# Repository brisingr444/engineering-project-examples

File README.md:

# engineering-project-examples
Editable sample projects for SynthCrew, Workcell Foundry, SiliconForge, PowerSystem and TraceForge.

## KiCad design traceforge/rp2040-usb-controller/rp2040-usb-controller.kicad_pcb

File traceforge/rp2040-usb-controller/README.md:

[Download this editable project ZIP](rp2040-usb-controller.zip)

Extract the complete project folder before opening it. The source files are also available below.

ZIP SHA-256: `ee8aa9aada79eca28375414765a2e70979933c8f12b47b56a6a397c69c7f46b1`

# RP2040 USB-C Bench DAQ / Controller

An editable, USB-powered RP2040 bench design with four analogue inputs, eight digital I/O, I2C and SWD. The design starts with the leads: each analogue input on J2 has its ground beside it. The USB-C receptacle sits on a short edge; digital and analogue headers are on opposite sides of the board.

## Open and inspect

Extract the entire directory together. Open **rp2040-usb-controller.kicad_pro** in TraceForge or KiCad 10.0.5 with the standard KiCad 10 symbols and footprints installed. Open the schematic to follow a channel, then open the PCB to inspect the copper. In the PCB editor choose **View → 3D Viewer** (Alt+3). The supplied render uses the exact STEP resources named in the board; it is not a photograph.

With the matching stock 3D libraries installed, the standard paths work. To use just this package’s fourteen models on Linux without changing your global path, start a single KiCad session from this directory:

```sh
KICAD10_3DMODEL_DIR="$PWD/models" kicad rp2040-usb-controller.kicad_pro
```

On Windows, open a fresh PowerShell in the extracted directory, set `$env:KICAD10_3DMODEL_DIR = (Resolve-Path .\models).Path`, and start your installed KiCad executable from that shell with the .kicad_pro file. Closing that shell leaves the normal system setting unchanged.

## At the bench

**This is an unbuilt design reference**, not a tested device. See [the design notes and numbered header guide](PROJECT.md) for signal limits and intended use; [Bench-BOM.csv](Bench-BOM.csv) is editable. There is no firmware. Do not backfeed the 3V3 output or assume protection for inputs outside the specified range. Perform your own fabrication, electrical, fit and bring-up reviews.

## What the checks cover

The supplied PCB and schematic were read with KiCad 10.0.5. Enabled ERC, DRC and schematic-to-board parity reported no findings; the DRC report recorded no unconnected items. All 42 footprint origins, including four mounting holes, were inside the rectangular board outline. The 38 fitted references use the fourteen unique STEP models supplied here. This post-run visual check supplements the original engineering notes: the creator sandbox did not itself contain the model library.

The native full candidate suite reported **14 passed, 0 failed, 9 skipped**. [The suite summary](checks/agent-checks.json) names each check. The KiCad reports preserve their ignored-check lists: [ERC](checks/erc.json) and [DRC and parity](checks/drc-parity.json). No hardware performance, impedance measurement, enclosure mating tolerance or USB certification is claimed.

[Licence and attribution](ATTRIBUTION.md) · [TraceForge app download](https://traceforge.space/download/)

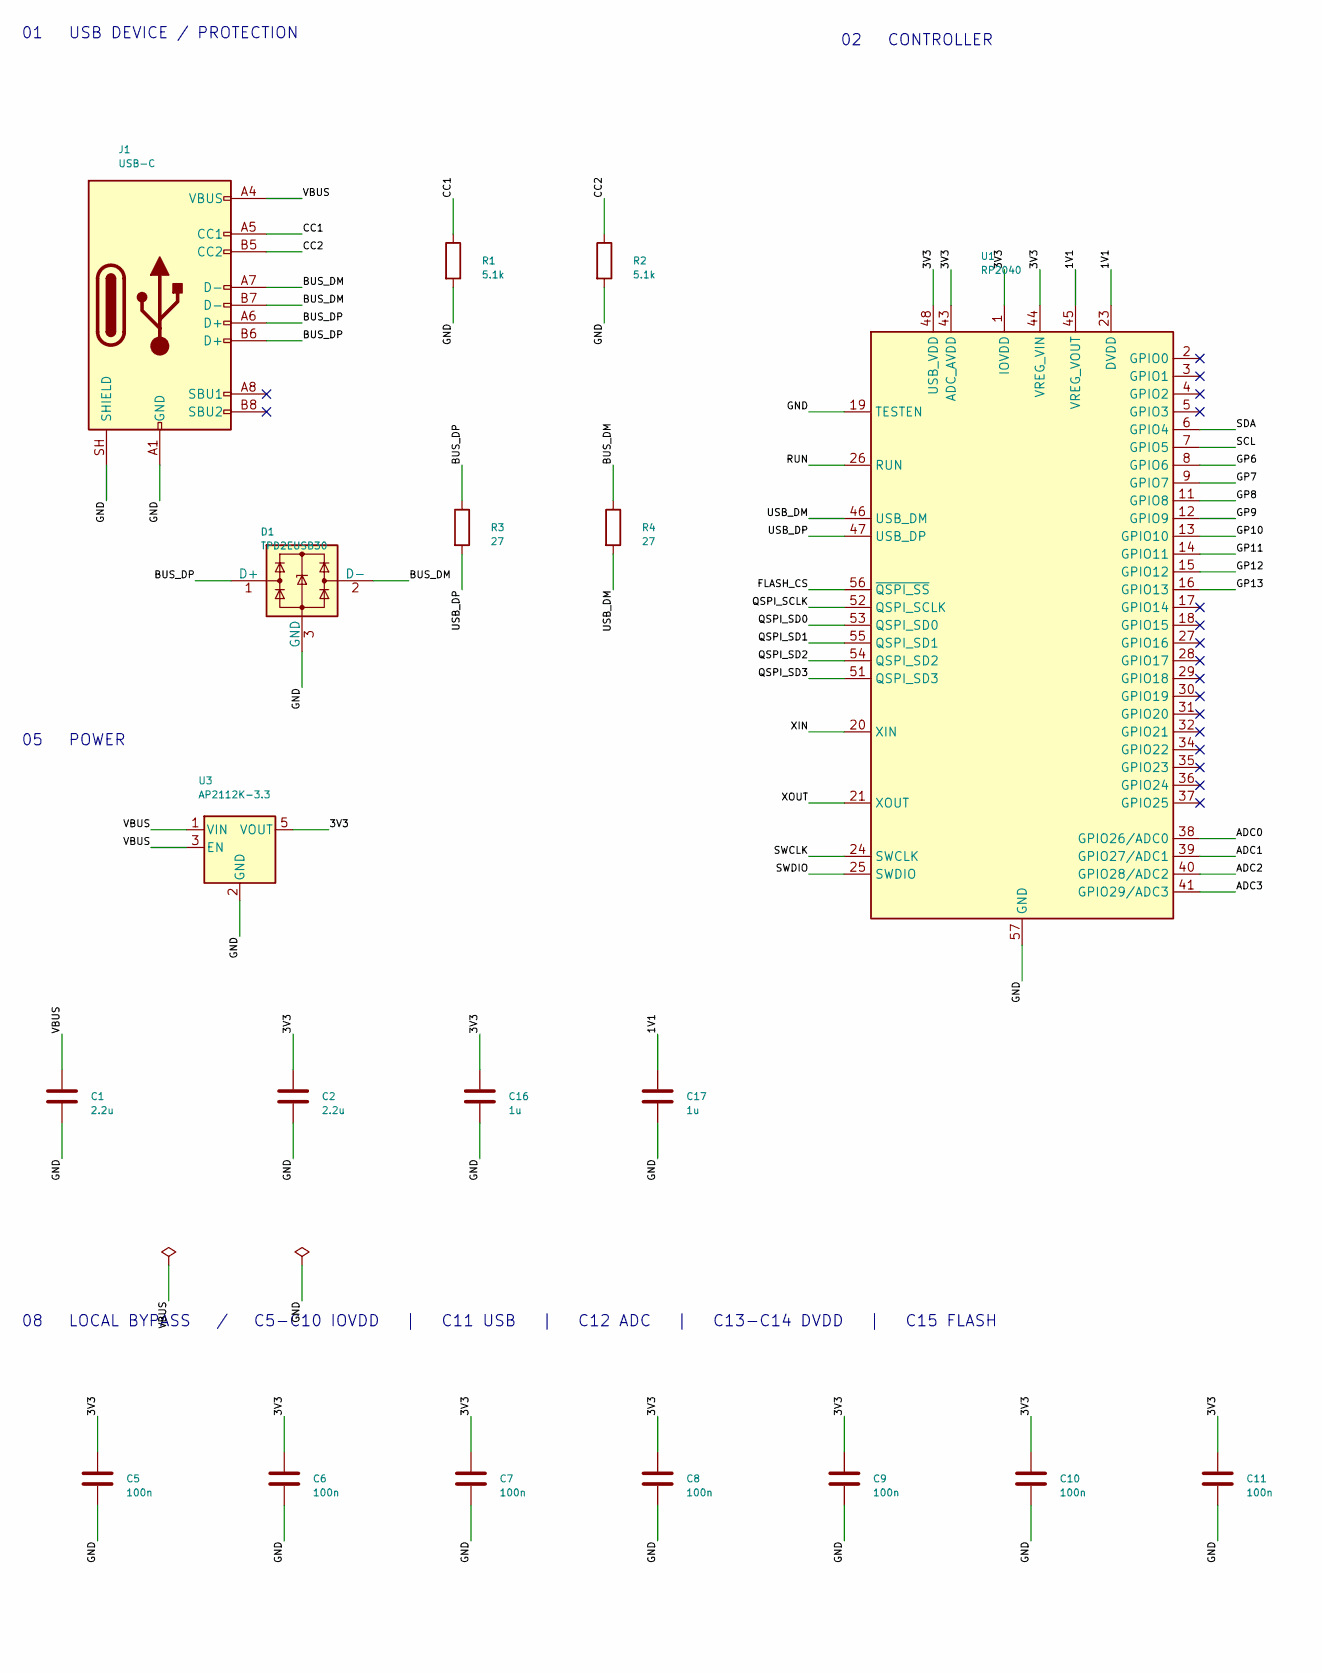
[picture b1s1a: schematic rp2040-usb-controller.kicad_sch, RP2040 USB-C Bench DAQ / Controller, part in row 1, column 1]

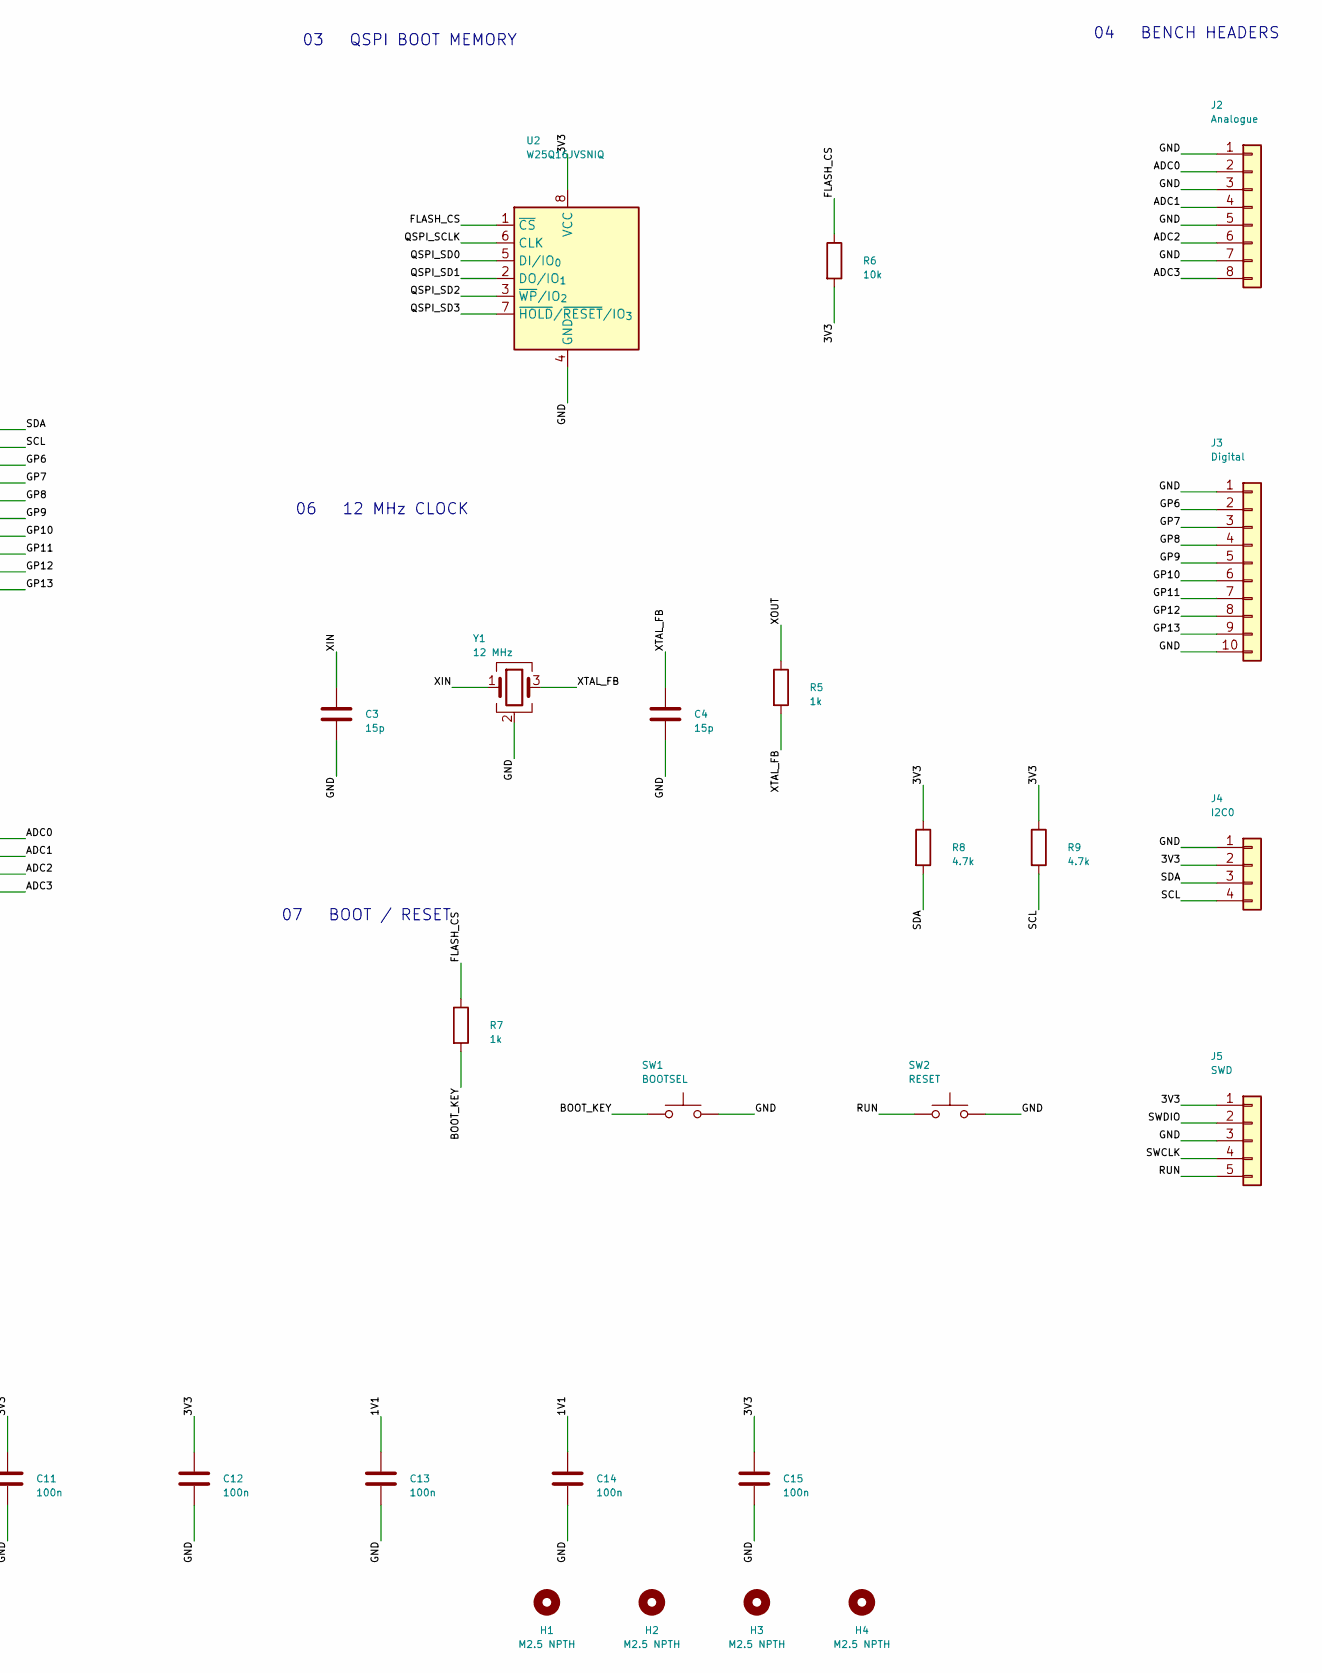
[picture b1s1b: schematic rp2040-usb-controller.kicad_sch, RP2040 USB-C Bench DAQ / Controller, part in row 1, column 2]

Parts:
C1, C2: 2.2u; C_0805_2012Metric; MPN GRM21BR71E225KA73L
C3, C4: 15p; C_0603_1608Metric; MPN GRM1885C1H150JA01D
C5, C6, C7, C8, C9, C10, C11, C12, C13, C14, C15: 100n; C_0603_1608Metric; MPN GRM188R71C104KA01D
C16, C17: 1u; C_0603_1608Metric; MPN GRM188R71C105KA12D
D1: TPD2EUSB30; Texas_DRT-3; MPN TPD2EUSB30DRTR
H1, H2, H3, H4: M2.5 NPTH; MountingHole_2.7mm_M2.5
J1: USB-C; USB_C_Receptacle_GCT_USB4085; MPN USB4085-GF-A
J2: Analogue; PinHeader_1x08_P2.54mm_Vertical; MPN TSW-008-07-G-S
J3: Digital; PinHeader_1x10_P2.54mm_Vertical; MPN TSW-010-07-G-S
J4: I2C0; PinHeader_1x04_P2.54mm_Vertical; MPN TSW-004-07-G-S
J5: SWD; PinHeader_1x05_P2.54mm_Vertical; MPN TSW-005-07-G-S
R1, R2: 5.1k; R_0603_1608Metric; MPN RC0603FR-075K1L
R3, R4: 27; R_0603_1608Metric; MPN RC0603FR-0727RL
R5, R7: 1k; R_0603_1608Metric; MPN RC0603FR-071KL
R6: 10k; R_0603_1608Metric; MPN RC0603FR-0710KL
R8, R9: 4.7k; R_0603_1608Metric; MPN RC0603FR-074K7L
SW1: BOOTSEL; SW_Push_1P1T_NO_CK_KMR2; MPN KMR221GLFS
SW2: RESET; SW_Push_1P1T_NO_CK_KMR2; MPN KMR221GLFS
U1: RP2040; QFN-56-1EP_7x7mm_P0.4mm_EP3.2x3.2mm; MPN RP2040
U2: W25Q16JVSNIQ; SOIC-8_3.9x4.9mm_P1.27mm; MPN W25Q16JVSNIQ
U3: AP2112K-3.3; SOT-23-5; MPN AP2112K-3.3TRG1
Y1: 12 MHz; Crystal_SMD_3225-4Pin_3.2x2.5mm; MPN ABM8-272-T3

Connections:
/1V1: C13.1, C14.1, C17.1, U1.23 (DVDD), U1.45 (VREG_VOUT), U1.50 (DVDD)
/3V3: C2.1, C5.1, C6.1, C7.1, C8.1, C9.1, C10.1, C11.1, C12.1, C15.1, C16.1, J4.2, J5.1, R6.2, R8.1, R9.1, U1.1 (IOVDD), U1.10 (IOVDD), U1.22 (IOVDD), U1.33 (IOVDD), U1.42 (IOVDD), U1.43 (ADC_AVDD), U1.44 (VREG_VIN), U1.48 (USB_VDD), U1.49 (IOVDD), U2.8 (VCC), U3.5 (VOUT)
/ADC0: J2.2, U1.38 (GPIO26/ADC0)
/ADC1: J2.4, U1.39 (GPIO27/ADC1)
/ADC2: J2.6, U1.40 (GPIO28/ADC2)
/ADC3: J2.8, U1.41 (GPIO29/ADC3)
/BOOT_KEY: R7.2, SW1.1
/BUS_DM: D1.2 (D-), J1.A7 (D-_A7), J1.B7 (D-_B7), R4.1
/BUS_DP: D1.1 (D+), J1.A6 (D+_A6), J1.B6 (D+_B6), R3.1
/CC1: J1.A5 (CC1_A5), R1.1
/CC2: J1.B5 (CC2_B5), R2.1
/FLASH_CS: R6.1, R7.1, U1.56 (~QSPI_SS), U2.1 (~CS)
/GND: C1.2, C2.2, C3.2, C4.2, C5.2, C6.2, C7.2, C8.2, C9.2, C10.2, C11.2, C12.2, C13.2, C14.2, C15.2, C16.2, C17.2, D1.3 (GND), J1.A1 (GND_A1), J1.A12 (GND_A12), J1.B1 (GND_B1), J1.B12 (GND_B12), J1.SH (SHIELD_S1), J2.1, J2.3, J2.5, J2.7, J3.1, J3.10, J4.1, J5.3, R1.2, R2.2, SW1.2, SW2.2, U1.19 (TESTEN), U1.57 (GND), U2.4 (GND), U3.2 (GND), Y1.2 (G), Y1.4 (G)
/GP6: J3.2, U1.8 (GPIO6)
/GP7: J3.3, U1.9 (GPIO7)
/GP8: J3.4, U1.11 (GPIO8)
/GP9: J3.5, U1.12 (GPIO9)
/GP10: J3.6, U1.13 (GPIO10)
/GP11: J3.7, U1.14 (GPIO11)
/GP12: J3.8, U1.15 (GPIO12)
/GP13: J3.9, U1.16 (GPIO13)
/QSPI_SCLK: U1.52 (QSPI_SCLK), U2.6 (CLK)
/QSPI_SD0: U1.53 (QSPI_SD0), U2.5 (DI/IO_{0})
/QSPI_SD1: U1.55 (QSPI_SD1), U2.2 (DO/IO_{1})
/QSPI_SD2: U1.54 (QSPI_SD2), U2.3 (~WP/IO_{2})
/QSPI_SD3: U1.51 (QSPI_SD3), U2.7 (~HOLD/~RESET/IO_{3})
/RUN: J5.5, SW2.1, U1.26 (RUN)
/SCL: J4.4, R9.2, U1.7 (GPIO5)
/SDA: J4.3, R8.2, U1.6 (GPIO4)
/SWCLK: J5.4, U1.24 (SWCLK)
/SWDIO: J5.2, U1.25 (SWDIO)
/USB_DM: R4.2, U1.46 (USB_DM)
/USB_DP: R3.2, U1.47 (USB_DP)
/VBUS: C1.1, J1.A4 (VBUS_A4), J1.A9 (VBUS_A9), J1.B4 (VBUS_B4), J1.B9 (VBUS_B9), U3.1 (VIN), U3.3 (EN)
/XIN: C3.1, U1.20 (XIN), Y1.1
/XOUT: R5.1, U1.21 (XOUT)
/XTAL_FB: C4.1, R5.2, Y1.3

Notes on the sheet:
01 USB DEVICE / PROTECTION
02 CONTROLLER
03 QSPI BOOT MEMORY
04 BENCH HEADERS
05 POWER
06 12 MHz CLOCK
07 BOOT / RESET
08 LOCAL BYPASS / C5-C10 IOVDD | C11 USB | C12 ADC | C13-C14 DVDD | C15 FLASH

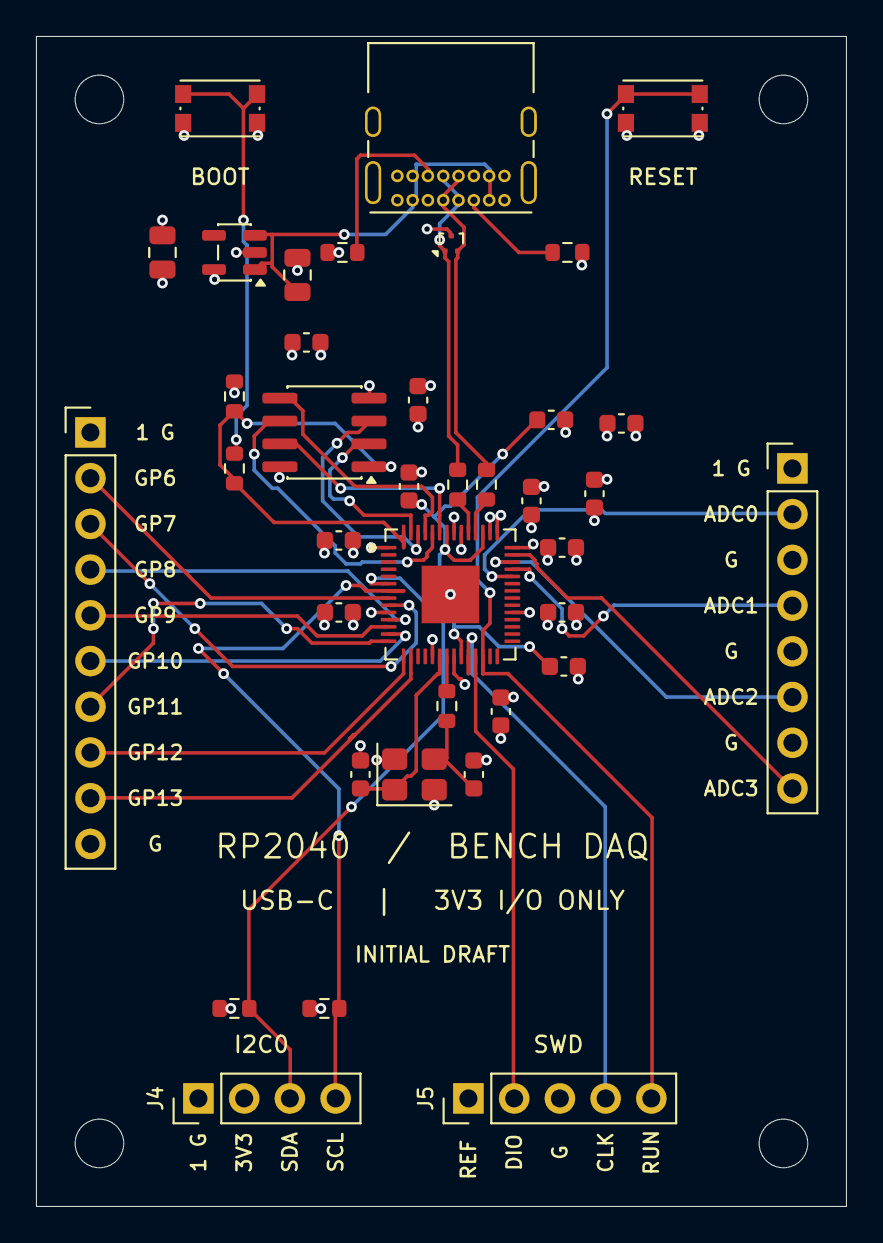
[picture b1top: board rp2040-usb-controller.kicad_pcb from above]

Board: 4 copper layers, 45.0 x 65.0 mm, 42 parts (0 on the bottom side), 37 nets.

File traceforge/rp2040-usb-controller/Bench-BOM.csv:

Reference,Quantity,Value,Manufacturer,MPN,Package,KiCad footprint,Source
C1,1,2.2u,Murata,GRM21BR71E225KA73L,C_0805_2012Metric,Capacitor_SMD:C_0805_2012Metric,https://www.murata.com/en-us/products/capacitor/ceramiccapacitor
C2,1,2.2u,Murata,GRM21BR71E225KA73L,C_0805_2012Metric,Capacitor_SMD:C_0805_2012Metric,https://www.murata.com/en-us/products/capacitor/ceramiccapacitor
C3,1,15p,Murata,GRM1885C1H150JA01D,C_0603_1608Metric,Capacitor_SMD:C_0603_1608Metric,https://www.murata.com/en-us/products/capacitor/ceramiccapacitor
C4,1,15p,Murata,GRM1885C1H150JA01D,C_0603_1608Metric,Capacitor_SMD:C_0603_1608Metric,https://www.murata.com/en-us/products/capacitor/ceramiccapacitor
C5,1,100n,Murata,GRM188R71C104KA01D,C_0603_1608Metric,Capacitor_SMD:C_0603_1608Metric,https://www.murata.com/en-us/products/capacitor/ceramiccapacitor
C6,1,100n,Murata,GRM188R71C104KA01D,C_0603_1608Metric,Capacitor_SMD:C_0603_1608Metric,https://www.murata.com/en-us/products/capacitor/ceramiccapacitor
C7,1,100n,Murata,GRM188R71C104KA01D,C_0603_1608Metric,Capacitor_SMD:C_0603_1608Metric,https://www.murata.com/en-us/products/capacitor/ceramiccapacitor
C8,1,100n,Murata,GRM188R71C104KA01D,C_0603_1608Metric,Capacitor_SMD:C_0603_1608Metric,https://www.murata.com/en-us/products/capacitor/ceramiccapacitor
C9,1,100n,Murata,GRM188R71C104KA01D,C_0603_1608Metric,Capacitor_SMD:C_0603_1608Metric,https://www.murata.com/en-us/products/capacitor/ceramiccapacitor
C10,1,100n,Murata,GRM188R71C104KA01D,C_0603_1608Metric,Capacitor_SMD:C_0603_1608Metric,https://www.murata.com/en-us/products/capacitor/ceramiccapacitor
C11,1,100n,Murata,GRM188R71C104KA01D,C_0603_1608Metric,Capacitor_SMD:C_0603_1608Metric,https://www.murata.com/en-us/products/capacitor/ceramiccapacitor
C12,1,100n,Murata,GRM188R71C104KA01D,C_0603_1608Metric,Capacitor_SMD:C_0603_1608Metric,https://www.murata.com/en-us/products/capacitor/ceramiccapacitor
C13,1,100n,Murata,GRM188R71C104KA01D,C_0603_1608Metric,Capacitor_SMD:C_0603_1608Metric,https://www.murata.com/en-us/products/capacitor/ceramiccapacitor
C14,1,100n,Murata,GRM188R71C104KA01D,C_0603_1608Metric,Capacitor_SMD:C_0603_1608Metric,https://www.murata.com/en-us/products/capacitor/ceramiccapacitor
C15,1,100n,Murata,GRM188R71C104KA01D,C_0603_1608Metric,Capacitor_SMD:C_0603_1608Metric,https://www.murata.com/en-us/products/capacitor/ceramiccapacitor
C16,1,1u,Murata,GRM188R71C105KA12D,C_0603_1608Metric,Capacitor_SMD:C_0603_1608Metric,https://www.murata.com/en-us/products/capacitor/ceramiccapacitor
C17,1,1u,Murata,GRM188R71C105KA12D,C_0603_1608Metric,Capacitor_SMD:C_0603_1608Metric,https://www.murata.com/en-us/products/capacitor/ceramiccapacitor
D1,1,TPD2EUSB30,Texas Instruments,TPD2EUSB30DRTR,Texas_DRT-3,Package_TO_SOT_SMD:Texas_DRT-3,https://www.ti.com/lit/ds/symlink/tpd2eusb30.pdf
J1,1,USB-C,GCT,USB4085-GF-A,USB_C_Receptacle_GCT_USB4085,Connector_USB:USB_C_Receptacle_GCT_USB4085,https://gct.co/connector/usb4085
J2,1,Analogue,Samtec,TSW-008-07-G-S,PinHeader_1x08_P2.54mm_Vertical,Connector_PinHeader_2.54mm:PinHeader_1x08_P2.54mm_Vertical,https://www.samtec.com/products/tsw
J3,1,Digital,Samtec,TSW-010-07-G-S,PinHeader_1x10_P2.54mm_Vertical,Connector_PinHeader_2.54mm:PinHeader_1x10_P2.54mm_Vertical,https://www.samtec.com/products/tsw
J4,1,I2C0,Samtec,TSW-004-07-G-S,PinHeader_1x04_P2.54mm_Vertical,Connector_PinHeader_2.54mm:PinHeader_1x04_P2.54mm_Vertical,https://www.samtec.com/products/tsw
J5,1,SWD,Samtec,TSW-005-07-G-S,PinHeader_1x05_P2.54mm_Vertical,Connector_PinHeader_2.54mm:PinHeader_1x05_P2.54mm_Vertical,https://www.samtec.com/products/tsw
R1,1,5.1k,Yageo,RC0603FR-075K1L,R_0603_1608Metric,Resistor_SMD:R_0603_1608Metric,https://www.yageo.com/
R2,1,5.1k,Yageo,RC0603FR-075K1L,R_0603_1608Metric,Resistor_SMD:R_0603_1608Metric,https://www.yageo.com/
R3,1,27,Yageo,RC0603FR-0727RL,R_0603_1608Metric,Resistor_SMD:R_0603_1608Metric,https://www.yageo.com/
R4,1,27,Yageo,RC0603FR-0727RL,R_0603_1608Metric,Resistor_SMD:R_0603_1608Metric,https://www.yageo.com/
R5,1,1k,Yageo,RC0603FR-071KL,R_0603_1608Metric,Resistor_SMD:R_0603_1608Metric,https://www.yageo.com/
R6,1,10k,Yageo,RC0603FR-0710KL,R_0603_1608Metric,Resistor_SMD:R_0603_1608Metric,https://www.yageo.com/
R7,1,1k,Yageo,RC0603FR-071KL,R_0603_1608Metric,Resistor_SMD:R_0603_1608Metric,https://www.yageo.com/
R8,1,4.7k,Yageo,RC0603FR-074K7L,R_0603_1608Metric,Resistor_SMD:R_0603_1608Metric,https://www.yageo.com/
R9,1,4.7k,Yageo,RC0603FR-074K7L,R_0603_1608Metric,Resistor_SMD:R_0603_1608Metric,https://www.yageo.com/
SW1,1,BOOTSEL,C&K,KMR221GLFS,SW_Push_1P1T_NO_CK_KMR2,Button_Switch_SMD:SW_Push_1P1T_NO_CK_KMR2,https://www.ckswitches.com/products/switches/product-details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
SW2,1,RESET,C&K,KMR221GLFS,SW_Push_1P1T_NO_CK_KMR2,Button_Switch_SMD:SW_Push_1P1T_NO_CK_KMR2,https://www.ckswitches.com/products/switches/product-details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
U1,1,RP2040,Raspberry Pi,RP2040,QFN-56-1EP_7x7mm_P0.4mm_EP3.2x3.2mm,Package_DFN_QFN:QFN-56-1EP_7x7mm_P0.4mm_EP3.2x3.2mm,https://datasheets.raspberrypi.com/rp2040/rp2040-datasheet.pdf
U2,1,W25Q16JVSNIQ,Winbond,W25Q16JVSNIQ,SOIC-8_3.9x4.9mm_P1.27mm,Package_SO:SOIC-8_3.9x4.9mm_P1.27mm,https://www.winbond.com/hq/product/code-storage-flash/qspi-n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
U3,1,AP2112K-3.3,Diodes Incorporated,AP2112K-3.3TRG1,SOT-23-5,Package_TO_SOT_SMD:SOT-23-5,https://www.diodes.com/datasheet/download/AP2112.pdf
Y1,1,12 MHz,Abracon,ABM8-272-T3,Crystal_SMD_3225-4Pin_3.2x2.5mm,Crystal:Crystal_SMD_3225-4Pin_3.2x2.5mm,https://abracon.com/datasheets/ABM8-272-T3.pdf
